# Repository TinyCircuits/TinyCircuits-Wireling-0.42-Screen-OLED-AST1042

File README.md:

# TinyCircuits Wireling 0.42 Screen OLED
# AST1042 Rev1

The design files are located under design_files/ for the TinyCircuits AST1042 Rev 1 PCB. This is a Wireling board which is the smallest our line has to offer, still packing an impressive 72 x 40 pixels in a 0.42" package for all your tiny display needs.

Format is in Cadsoft Eagle format - Eagle version 6.2 was used for the original design.

For more infomation on this, check out the product page at TinyCircuits.com

# License:

Design by TinyCircuits.
All design files are released under the Creative Commons Attribution Share-Alike 3.0 License, see the following link for details: http://creativecommons.org/licenses/by-sa/3.0

All text above must be included in any redistribution or derived design

This project uses designs and concepts developed as part of the Arduino project and the LilyPad project.  The TinyCircuits design files themselves (schematics, PCB and libraries) are not directly derived from these works' design files and have been created new, however the concepts and basic architecture behind the TinyDuino and TinyLily products are derived and we thank the hard work of the organizations below for their contributions to open-source hardware:
  
Original Arduino Uno Design by Team Arduino

LilyPad Arduino Design by Leah Buechley and Sparkfun Electronics

Please support the open-source hardware community

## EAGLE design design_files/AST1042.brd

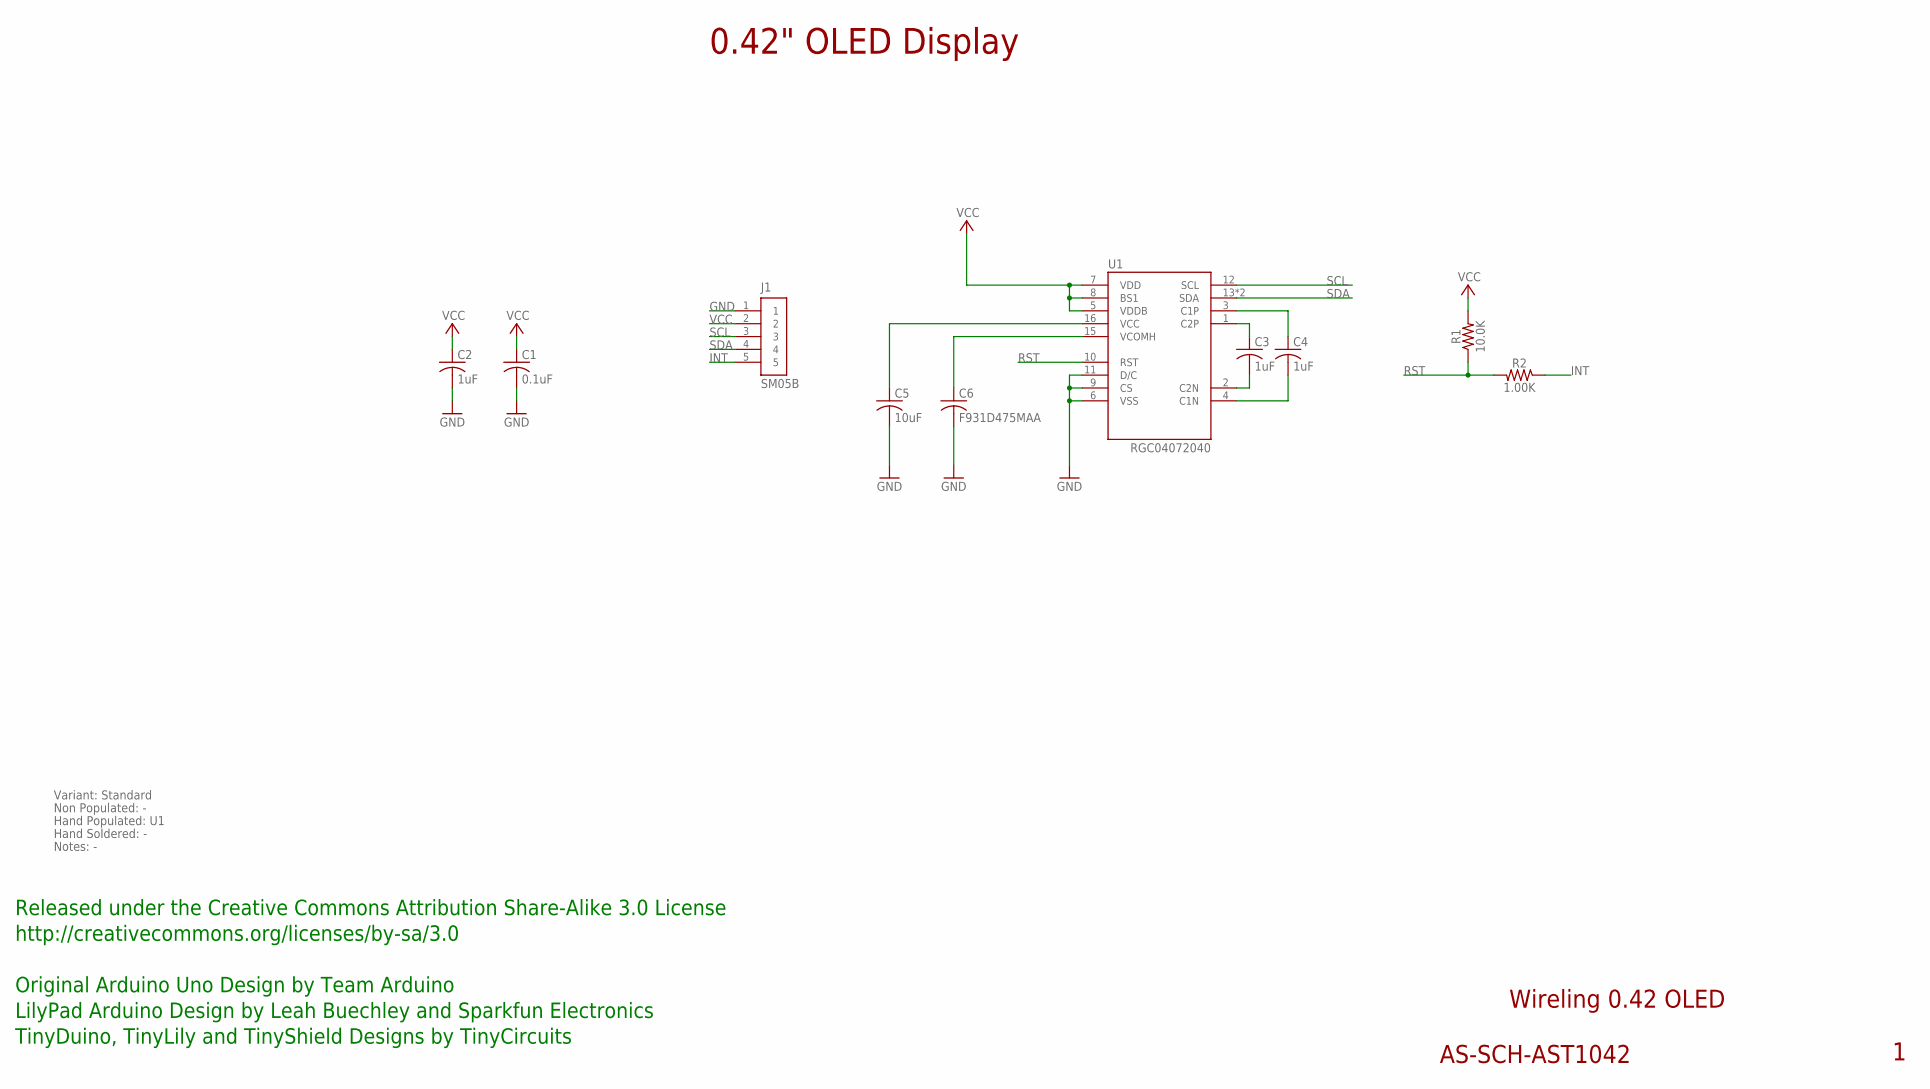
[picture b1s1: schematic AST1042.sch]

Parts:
C1: 0.1uF; C0402
C2: 1uF; C0603; PARTNO AS-ITM-00410
C3, C4: 1uF; C0603
C5: 10uF; C0805
C6: F931D475MAA; 1206_CAP_TANT
J1: SM05B; JST_SH_5X1_EDGE
R1: 10.0K; 0402
R2: 1.00K; 0402; PARTNO AS-ITM-00003
U1: RGC04072040; OLED_042

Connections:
GND: C1.2, C2.2, C5.2, C6.2, J1.1, U1.6 (VSS), U1.9 (CS), U1.11 (D/C)
INT: J1.5, R2.1
unnamed: C6.1, U1.15 (VCOMH)
unnamed: C3.1, U1.1 (C2P)
unnamed: C5.1, U1.16 (VCC)
unnamed: C4.1, U1.3 (C1P)
unnamed: C3.2, U1.2 (C2N)
unnamed: C4.2, U1.4 (C1N)
RST: R1.1, R2.2, U1.10 (RST)
SCL: J1.3, U1.12 (SCL)
SDA: J1.4, U1.13 (SDA), U1.14 (SDA)
VCC: C1.1, C2.1, J1.2, R1.2, U1.5 (VDDB), U1.7 (VDD), U1.8 (BS1)

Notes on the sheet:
Wireling 0.42 OLED
AS-SCH-AST1042
0.42" OLED Display
Released under the Creative Commons Attribution Share-Alike 3.0 License
http://creativecommons.org/licenses/by-sa/3.0
Original Arduino Uno Design by Team Arduino
TinyDuino, TinyLily and TinyShield Designs by TinyCircuits
LilyPad Arduino Design by Leah Buechley and Sparkfun Electronics
Non Populated: -
Hand Populated: U1
Hand Soldered: -
Variant: Standard
Notes: -

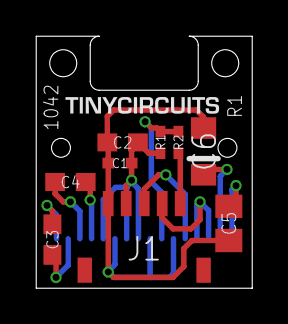
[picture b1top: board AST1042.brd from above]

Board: 2 copper layers, 12.0 x 14.0 mm, 11 parts (1 on the bottom side), 12 nets.

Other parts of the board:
U$1: DOCFIELD-TINYCIRCUITS-PCB

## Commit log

2019-08-02 added example sketches
2019-08-07 added .zip to libraries folder
2019-08-15 added datasheet
2019-11-14 update naming
2019-12-03 pics
2019-12-03 code
2020-01-16 gifs~!
2020-02-04 mass image update
2020-02-27 fix lib
2020-05-05 example
2020-08-14 Add CAD data
